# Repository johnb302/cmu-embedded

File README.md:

# cmu-embedded

Zephyr firmware for a small RC car on an **STM32 Nucleo-F401RE**.

A Raspberry Pi reads a steering wheel + pedals and sends commands over UART.
The Nucleo turns those into motor speed, steering, and blinkers — and stops the car safely if the Pi goes quiet.

```
 Steering wheel / pedals
          │
          ▼
   Raspberry Pi ──UART (13-byte frames)──▶ Nucleo F401RE ──▶ motors, servo, blinkers
          ▲                                     │
          └────────── status frames ────────────┘  (current sensors, error state)
```

## File tree

```
.
├── CMakeLists.txt          # What gets compiled (normal firmware or a calibration build)
├── prj.conf                # Zephyr features to enable (GPIO, PWM, ADC, UART, logging)
├── prj_lab3.conf           # Zephyr features for Lab 3 (CAN)
├── zephyr-env.sh           # Sets paths to the local Zephyr SDK/toolchain in .tools/
├── boards/
│   ├── nucleo_f401re.overlay       # Pin map: motors, encoders, servo, blinkers, ADC, UART
│   └── nucleo_f401re_lab3.overlay  # Lab 3 pin map: MCP2515 CAN over SPI
├── src/
│   ├── config.h            # ★ Every tunable number: timings, PID gains, pedal ranges, priorities
│   ├── main.c              # ★ Start here. Receives Pi frames, runs the link watchdog
│   ├── motor_control.c/h   # PID speed loop: pedals → target RPM → PWM
│   ├── motor_driver.c/h    # Low-level L298N H-bridge (drive / brake / coast)
│   ├── encoder.c/h         # Wheel encoders → position + RPM
│   ├── servo_driver.c/h    # Steering servo: steering value → pulse width
│   ├── blinker.c/h         # Turn signals and hazards
│   ├── wheel_buttons.c/h   # Debounces steering-wheel buttons
│   ├── status_tx.c/h       # Sends status frames back to the Pi
│   └── crc8_checksum.h     # CRC-8 shared with the Pi
├── src_lab3/               # Lab 3 dual CAN-bus firmware (built with -DCAN_LAB=ON)
│   ├── lab3.c              # Entry point: N2 steering / N3 drivetrain, chosen by NODE_ID
│   ├── can_bus.c/h         # MCP2515 dual-bus CAN: filters, TX/RX, stall recovery
│   ├── zone_state.c/h      # This zone's OK/ERROR state machine
│   ├── heartbeat.c/h       # Heartbeat TX + monitoring of other zones
│   ├── watchdog.c/h        # Independent watchdog (IWDG), fed only while tasks make progress
│   ├── control.c/h, blink.c/h, button.c/h, n2_tasks.c/h
│   └── tasks.h             # Per-node thread priorities
├── tools/
│   ├── telemetry/          # Live USB dashboard (Python + Matplotlib), logs CSV
│   ├── motor_calibration/  # Separate firmware + script to sweep motor PWM
│   └── servo_calibration/  # Separate firmware + script to find servo endpoints
├── Lab2_Writeup.pdf        # Lab 2 report
└── tests.yaml              # Leftover from the Zephyr blinky sample
```

★ = read these first.

## How the firmware works

Everything runs as Zephyr threads. Lower number = higher priority.

| Priority | Thread         | Job |
| -------: | -------------- | --- |
| 0 | motor          | Every 10 ms: read encoders, run PID, set PWM |
| 1 | fail_safe      | Wakes only if the Pi stops talking → brake + hazards |
| 2 | cmd_handler    | One run per Pi frame: check CRC, apply steer/throttle/brake |
| 3 | status_tx      | Every 20 ms: send current readings + state to the Pi |
| 4 | blinker        | Flashes turn signals / hazards |

One command's path:

1. **UART interrupt** (`main.c`) assembles a 13-byte frame and queues it (only the newest is kept).
2. **cmd_handler** checks the CRC and value ranges, then hands throttle/brake to `motor_control` and steering to `servo_driver`.
3. **Link watchdog**: each good frame restarts a timer. Three missed 50 ms intervals → **fail-safe** (brake, steering off, hazards on).
4. Bad or out-of-range values also trigger fail-safe. The car powers up in fail-safe until the first valid frame.

Frame layout (both directions): `SOF(0xA5) | ID(2) | DLC | data(8) | CRC`.
Command data = steer, throttle, brake (int16 LE), buttons, sequence number.

## Build and flash

```bash
source .venv/bin/activate          # also loads zephyr-env.sh
west build -b nucleo_f401re -p     # normal firmware
west flash
```

Calibration firmware (pick one):

```bash
west build -b nucleo_f401re -p -- -DMOTOR_CALIBRATION=ON
west build -b nucleo_f401re -p -- -DSERVO_CALIBRATION=ON
```

Lab 3 CAN firmware (`src_lab3/`), one build per node:

```bash
west build -b nucleo_f401re -p -d build-lab3-n2 -- -DCAN_LAB=ON -DNODE_ID=2 \
  -DCONF_FILE=prj_lab3.conf -DDTC_OVERLAY_FILE=boards/nucleo_f401re_lab3.overlay
```

Watch it run:

```bash
pip install -r tools/telemetry/requirements.txt
python -u tools/telemetry/telemetry.py --port /dev/ttyACM0
```

## Where to change things

| I want to…                         | Edit |
| ---------------------------------- | ---- |
| Tune PID, max RPM, timeouts        | `src/config.h` |
| Change which pin does what         | `boards/nucleo_f401re.overlay` |
| Turn a Zephyr driver on/off        | `prj.conf` |
| Change frame format                | `src/config.h` **and** the Pi sender |

Motor measurement notes live in `tools/motor_calibration/MEASUREMENTS.md`.

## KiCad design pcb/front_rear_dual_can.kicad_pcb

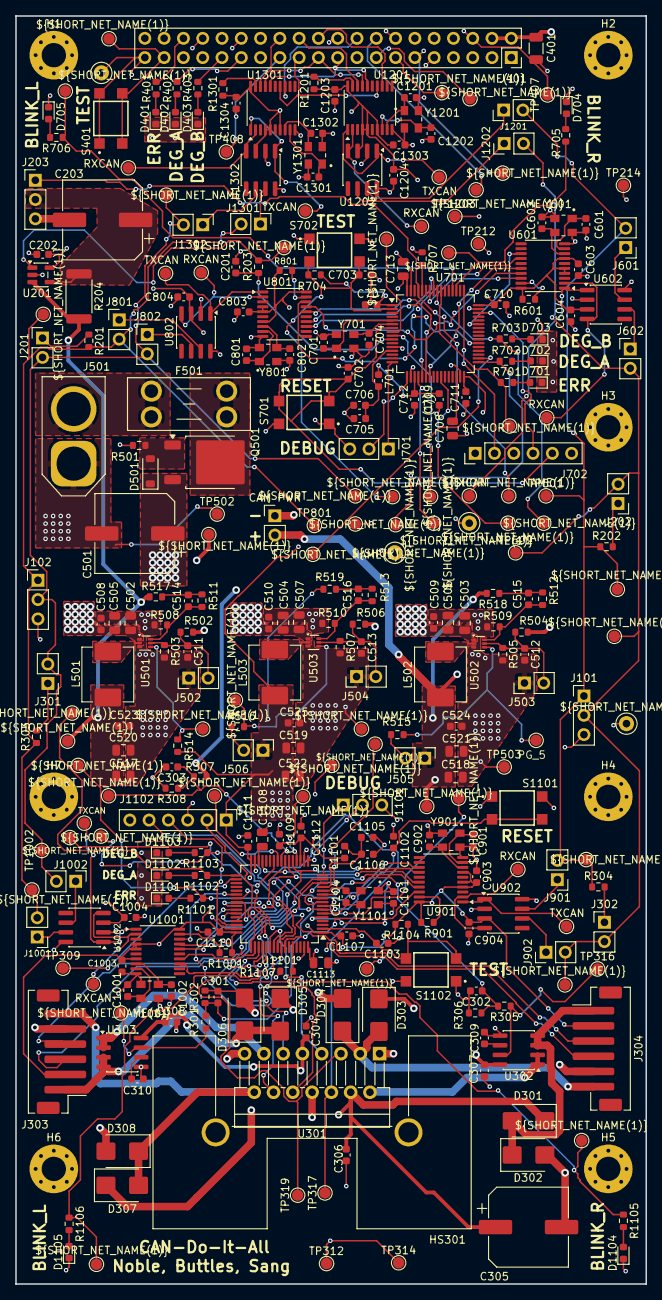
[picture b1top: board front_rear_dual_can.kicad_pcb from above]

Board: 4 copper layers, 83.0 x 167.0 mm, 328 parts (0 on the bottom side), 187 nets.

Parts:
C201, C202, C301, C302, C303, C304, C306, C307, C308, C508, C509, C510, C523, C524, C525, C603, C604, C702, C703, C706, C707, C709, C710, C711, C712, C803, C804, C903, C904, C1003, C1004, C1102, C1103, C1106, C1107, C1109, C1110, C1111, C1112, C1203, C1204, C1303, C1304: 100nF; C_0603_1608Metric
C203, C305, C501: 470μF; CP_Elec_10x12.6
C309, C310: 1nF; C_0603_1608Metric
C401: 47μF; C_1206_3216Metric
C502, C503, C504, C505, C506, C507: 10μF; C_0805_2012Metric
C511, C512, C513: 10nF; C_0603_1608Metric
C514: 33pF; C_0603_1608Metric
C515, C516: 30pF; C_0603_1608Metric
C517, C518, C519, C520, C521, C522: 22μF; C_0805_2012Metric
C601, C602, C701, C704, C801, C802, C901, C902, C1001, C1002, C1101, C1104, C1201, C1202, C1301, C1302: 22pF; C_0603_1608Metric
C705, C1105: 1μF; C_0603_1608Metric
C708, C713, C1108, C1113: 4.7μF; C_0805_2012Metric
CAM PWR: Conn_01x02; PinHeader_1x02_P2.54mm_Vertical
D301, D302, D303, D304, D305, D306, D307, D308: D_Schottky; D_SMB
D401, D402, D403, D701, D702, D703, D704, D705, D1101, D1102, D1103, D1104, D1105: LED; LED_0603_1608Metric
D501: BZT52C10; D_SOD-123
F501: 15A; Fuseholder_Blade_Mini_Keystone_3568
H1, H2, H3, H4, H5, H6, H7: MountingHole_3.2mm_M3_Pad_Via
HS301: HSINK_6396BG
J101: CAN A Connector; PinHeader_1x03_P2.54mm_Vertical
J102: CAN B Connector; PinHeader_1x03_P2.54mm_Vertical
J201, J202, J301, J302, J502, J503, J504, J505, J506: Conn_01x02; PinHeader_1x02_P2.54mm_Vertical
J203, J701, J1101: Conn_01x03; PinHeader_1x03_P2.54mm_Vertical
J303, J304: Conn_01x06; JST_PH_B6B-PH-SM4-TB_1x06-1MP_P2.00mm_Vertical
J401: Raspberry_Pi_4; PinSocket_2x20_P2.54mm_Vertical
J501: XT60; AMASS_XT60-M_1x02_P7.20mm_Vertical
J601, J602, J801, J802, J901, J902, J1001, J1002, J1201, J1202, J1301, J1302: Conn_01x02_Pin; PinHeader_1x02_P2.54mm_Vertical
J702, J1102: Conn_01x06; PinHeader_1x06_P2.54mm_Vertical
L501: 6.8μH; L_Sunlord_MWSA0603S
L502: 4.7μH; L_Sunlord_MWSA0603S
L503: 3.3μH; L_Sunlord_MWSA0603S
L701, L1101: L_Ferrite; L_0603_1608Metric
Q501: IPD90P03P4L-04-HXY; TO-252-2
R201, R202, R303, R304: 120Ω; R_0603_1608Metric
R203: 1kΩ; R_0603_1608Metric
R204: 40mΩ; R_2512_6332Metric
R301, R305, R308, R501, R503, R505, R507, R510, R514, R515, R516, R601, R704, R707, R801, R901, R1001, R1104, R1107, R1201, R1301: 10kΩ; R_0603_1608Metric
R302, R306: 20kΩ; R_0603_1608Metric
R307, R502, R504, R506: 47kΩ; R_0603_1608Metric
R401, R402, R403, R701, R702, R703, R705, R706, R1101, R1102, R1103, R1105, R1106: 330Ω; R_0603_1608Metric
R508, R509: 30kΩ; R_0603_1608Metric
R511: 348kΩ; R_0603_1608Metric
R512: 220kΩ; R_0603_1608Metric
R513: 45.3kΩ; R_0603_1608Metric
R517, R518, R519: 0Ω; R_0603_1608Metric
S401, S701, S702, S1101, S1102: SWT0210-045026GSA_REVA; SW_SWT0210-045026GSA_REVA
TP201, TP202, TP203, TP204, TP205, TP206, TP207, TP208, TP209, TP210, TP211, TP212, TP213, TP214, TP215, TP301, TP302, TP303, TP304, TP305, TP306, TP307, TP308, TP309, TP310, TP311, TP312, TP313, TP314, TP315, TP316, TP317, TP318, TP319, TP402, TP404, TP405, TP406, TP407, TP408, TP410, TP501, TP502, TP503, TP504, TP505, TP506, TP507, TP508, TP509, TP510, TP601, TP602, TP604, TP605, TP801, TP802, TP803, TP804, TP805, TP901, TP902, TP904, TP905, TP1001, TP1002, TP1004, TP1005, TP1201, TP1202, TP1203, TP1204, TP1205, TP1301, TP1302, TP1304, TP1305: TestPoint; TestPoint_Pad_D1.5mm
TP603, TP903, TP1003, TP1303: TestPoint; TestPoint_Keystone_5000-5004_Miniature
U201: INA180A1; SOT-23-5
U301: L298N; TO-220-15_P2.54x5.08mm_StaggerOdd_Lead4.58mm_Vertical
U302, U303: ACS712xLCTR-05B; SOIC-8_3.9x4.9mm_P1.27mm
U501, U502, U503: TPS564252DRLR; SOT-563
U601, U801, U901, U1001, U1201, U1301: MCP2515-xST; TSSOP-20_4.4x6.5mm_P0.65mm
U602, U802, U902, U1002, U1202, U1302: SN65HVD230; SOIC-8_3.9x4.9mm_P1.27mm
U701, U1101: STM32F401RETx; LQFP-64_10x10mm_P0.5mm
Y601, Y701, Y801, Y901, Y1001, Y1101, Y1201, Y1301: CX3225SB16000H0FLJCC; OSCCC320X250X60N

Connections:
+3V3: C202.1, C519.1, C522.1, C525.1, C603.2, C604.1, C707.2, C709.2, C710.1, C711.2, C712.2, C713.1, C803.2, C804.1, C903.2, C904.1, C1003.2, C1004.1, C1107.2, C1109.2, C1110.1, C1111.2, C1112.2, C1113.1, C1203.2, C1204.1, C1303.2, C1304.1, J303.2, J304.2, J506.1, J702.1, J1102.1, L503.2, L701.1, L1101.1, R514.2, R519.2, R601.1, R704.2, R801.1, R901.1, R1001.1, R1104.2, R1201.1, R1301.1, TP510.1 (1_1), U201.5 (V+), U601.4 (~TX0RTS), U601.5 (~TX1RTS), U601.7 (~TX2RTS), U601.20 (VDD), U602.3 (VCC), U701.1 (VBAT), U701.19 (VDD), U701.32 (VDD), U701.48 (VDD), U701.64 (VDD), U801.4 (~TX0RTS), U801.5 (~TX1RTS), U801.7 (~TX2RTS), U801.20 (VDD), U802.3 (VCC), U901.4 (~TX0RTS), U901.5 (~TX1RTS), U901.7 (~TX2RTS), U901.20 (VDD), U902.3 (VCC), U1001.4 (~TX0RTS), U1001.5 (~TX1RTS), U1001.7 (~TX2RTS), U1001.20 (VDD), U1002.3 (VCC), U1101.1 (VBAT), U1101.19 (VDD), U1101.32 (VDD), U1101.48 (VDD), U1101.64 (VDD), U1201.4 (~TX0RTS), U1201.5 (~TX1RTS), U1201.7 (~TX2RTS), U1201.20 (VDD), U1202.3 (VCC), U1301.4 (~TX0RTS), U1301.5 (~TX1RTS), U1301.7 (~TX2RTS), U1301.20 (VDD), U1302.3 (VCC)
+5V: C304.2, C307.1, C308.1, C401.1, C518.1, C521.1, C524.1, CAM PWR.2, J401.2 (5V), J401.4 (5V), J505.1, L502.2, R518.2, TP509.1 (1_1), U301.9 (Vss), U302.8 (VCC), U303.8 (VCC)
+7.5V: C517.1, C520.1, C523.1, L501.2, R204.2, R517.2, TP508.1 (1_1), U201.3 (+)
+12V: C305.1, C306.1, C501.1, C502.1, C503.1, C504.1, C505.1, C506.1, C507.1, C508.1, C509.1, C510.1, D301.1 (K), D303.1 (K), D305.1 (K), D307.1 (K), D501.1 (K), Q501.3 (S), R307.1, R502.1, R504.1, R506.1, TP501.1 (1_1), U301.4 (Vs), U501.1 (VIN), U502.1 (VIN), U503.1 (VIN)
/CAN_A+: J101.1, J601.2, J901.2, J1201.2, R202.1, R304.1, TP601.1 (1_1), TP901.1 (1_1), TP1201.1 (1_1)
/CAN_A-: J101.2, J202.2, J302.2, J602.2, J902.2, J1202.2, TP602.1 (1_1), TP902.1 (1_1), TP1202.1 (1_1)
/CAN_B+: J102.1, J801.2, J1001.2, J1301.2, R201.1, R303.1, TP801.1 (1_1), TP1001.1 (1_1), TP1301.1 (1_1)
/CAN_B-: J102.2, J201.2, J301.2, J802.2, J1002.2, J1302.2, TP802.1 (1_1), TP1002.1 (1_1), TP1302.1 (1_1)
/Cockpit/CAN A/CAN_H_Local: J1201.1, U1202.7 (CANH)
/Cockpit/CAN A/CAN_L_Local: J1202.1, U1202.6 (CANL)
/Cockpit/CAN A/CS: J401.24 (~CE0_SPI0/GPIO08), U1201.18 (~CS)
/Cockpit/CAN A/INT: J401.22 (GPIO25/SDIO_DAT1), U1201.13 (~INT)
/Cockpit/CAN A/OSC1: C1201.1, U1201.9 (OSC1), Y1201.1
/Cockpit/CAN A/OSC2: C1202.1, U1201.8 (OSC2), Y1201.3
/Cockpit/CAN A/SCK: J401.23 (SCLK_SPI0/GPIO11), U1201.14 (SCK), U1301.14 (SCK)
/Cockpit/CAN A/SI: J401.19 (MOSI_SPI0/GPIO10), U1201.16 (SI), U1301.16 (SI)
/Cockpit/CAN A/SO: J401.21 (MISO_SPI0/GPIO09), U1201.17 (SO), U1301.17 (SO)
/Cockpit/CAN B/CAN_H_Local: J1301.1, U1302.7 (CANH)
/Cockpit/CAN B/CAN_L_Local: J1302.1, U1302.6 (CANL)
/Cockpit/CAN B/CS: J401.26 (~CE1_SPI0/GPIO07), U1301.18 (~CS)
/Cockpit/CAN B/INT: J401.18 (GPIO24/SDIO_DAT0), U1301.13 (~INT)
/Cockpit/CAN B/OSC1: C1301.1, U1301.9 (OSC1), Y1301.1
/Cockpit/CAN B/OSC2: C1302.1, U1301.8 (OSC2), Y1301.3
/Cockpit/CAN_TX_A: J401.15 (GPIO22/SDIO_CLK), TP404.1 (1_1)
/Cockpit/CAN_TX_B: J401.16 (GPIO23/SDIO_CMD), TP406.1 (1_1)
/Cockpit/CMD_TX: J401.13 (GPIO27/SDIO_DAT3), TP402.1 (1_1)
/Cockpit/DEG_A: J401.29 (GPCLK1/GPIO05), R402.1
/Cockpit/DEG_B: J401.31 (GPCLK2/GPIO06), R403.1
/Cockpit/ERR: J401.36 (GPIO16/SPI1_~CE2), R401.1
/Cockpit/TEST_BTN: J401.37 (GPIO26/SDIO_DAT2), S401.3, S401.4, TP410.1 (1_1)
/Cockpit/UDP_RX: J401.11 (GPIO17/SPI1_~CE1), TP405.1 (1_1)
/Front Zone/BLINK_L: R706.1, TP208.1 (1_1), U701.52 (PC11)
/Front Zone/BLINK_R: R705.1, TP210.1 (1_1), U701.51 (PC10)
/Front Zone/CAN A/CAN_H_Local: J601.1, U602.7 (CANH)
/Front Zone/CAN A/CAN_L_Local: J602.1, U602.6 (CANL)
/Front Zone/CAN A/CS: U601.18 (~CS), U701.58 (PB6)
/Front Zone/CAN A/INT: U601.13 (~INT), U701.43 (PA10)
/Front Zone/CAN A/OSC1: C601.1, U601.9 (OSC1), Y601.1
/Front Zone/CAN A/OSC2: C602.1, U601.8 (OSC2), Y601.3
/Front Zone/CAN A/SCK: U601.14 (SCK), U701.21 (PA5), U801.14 (SCK)
/Front Zone/CAN A/SI: U601.16 (SI), U701.23 (PA7), U801.16 (SI)
/Front Zone/CAN A/SO: U601.17 (SO), U701.22 (PA6), U801.17 (SO)
/Front Zone/CAN B/CAN_H_Local: J801.1, U802.7 (CANH)
/Front Zone/CAN B/CAN_L_Local: J802.1, U802.6 (CANL)
/Front Zone/CAN B/CS: U701.38 (PC7), U801.18 (~CS)
/Front Zone/CAN B/INT: U701.57 (PB5), U801.13 (~INT)
/Front Zone/CAN B/OSC1: C801.1, U801.9 (OSC1), Y801.1
/Front Zone/CAN B/OSC2: C802.1, U801.8 (OSC2), Y801.3
/Front Zone/CAN_RX_A: TP202.1 (1_1), U701.26 (PB0)
/Front Zone/CAN_RX_B: TP203.1 (1_1), U701.9 (PC1)
/Front Zone/CAN_TX_A: TP205.1 (1_1), U701.8 (PC0)
/Front Zone/CAN_TX_B: TP207.1 (1_1), U701.20 (PA4)
/Front Zone/DEG_A: R702.1, TP204.1 (1_1), U701.33 (PB12)
/Front Zone/DEG_B: R703.1, TP206.1 (1_1), U701.56 (PB4)
/Front Zone/ERR: R701.1, TP201.1 (1_1), U701.55 (PB3)
/Front Zone/I_OUT: R203.2, TP215.1 (1_1), U201.1
/Front Zone/MCU/ADC1_12: C201.1, R203.1, U701.10 (PC2)
/Front Zone/MCU/OSC_IN: C701.1, U701.5 (PH0), Y701.1
/Front Zone/MCU/OSC_OUT: C704.1, U701.6 (PH1), Y701.3
/Front Zone/MCU/RST: C702.2, J702.5, S701.3, S701.4, U701.7 (NRST)
/Front Zone/MCU/SWCLK: J702.2, U701.49 (PA14)
/Front Zone/MCU/SWDIO: J702.4, U701.46 (PA13)
/Front Zone/MCU/USART_RX: J701.2, U701.17 (PA3)
/Front Zone/MCU/USART_TX: J701.1, U701.16 (PA2)
/Front Zone/RELAY: TP209.1 (1_1), U701.34 (PB13)
/Front Zone/SRV: J203.1, TP211.1 (1_1), U701.61 (PB8)
/Front Zone/TEST_BTN: C703.2, R704.1, S702.3, S702.4, TP213.1 (1_1), U701.2 (PC13)
/Power/PG_3.3: R516.1, TP506.1 (1_1), U503.4 (PG)
/Power/PG_5: R515.1, TP507.1 (1_1), U502.4 (PG)
/Power/PG_7.5: R514.1, TP505.1 (1_1), U501.4 (PG)
/Power/SW_3.3: L503.1, U503.2 (SW)
/Power/SW_5: L502.1, U502.2 (SW)
/Power/SW_7.5: L501.1, U501.2 (SW)
/Rear Zone/ADC_IN_L: C301.1, R301.2, R302.1, U1101.10 (PC2)
/Rear Zone/ADC_IN_R: C302.1, R305.2, R306.1, U1101.11 (PC3)
/Rear Zone/BLINK_L: R1106.1, TP308.1 (1_1), U1101.52 (PC11)
/Rear Zone/BLINK_R: R1105.1, TP310.1 (1_1), U1101.51 (PC10)
/Rear Zone/CAN A/CAN_H_Local: J901.1, U902.7 (CANH)
/Rear Zone/CAN A/CAN_L_Local: J902.1, U902.6 (CANL)
/Rear Zone/CAN A/CS: U901.18 (~CS), U1101.58 (PB6)
/Rear Zone/CAN A/INT: U901.13 (~INT), U1101.43 (PA10)
/Rear Zone/CAN A/OSC1: C901.1, U901.9 (OSC1), Y901.1
/Rear Zone/CAN A/OSC2: C902.1, U901.8 (OSC2), Y901.3
/Rear Zone/CAN A/SCK: U901.14 (SCK), U1001.14 (SCK), U1101.21 (PA5)
/Rear Zone/CAN A/SI: U901.16 (SI), U1001.16 (SI), U1101.23 (PA7)
/Rear Zone/CAN A/SO: U901.17 (SO), U1001.17 (SO), U1101.22 (PA6)
/Rear Zone/CAN B/CAN_H_Local: J1001.1, U1002.7 (CANH)
/Rear Zone/CAN B/CAN_L_Local: J1002.1, U1002.6 (CANL)
/Rear Zone/CAN B/CS: U1001.18 (~CS), U1101.38 (PC7)
/Rear Zone/CAN B/INT: U1001.13 (~INT), U1101.57 (PB5)
/Rear Zone/CAN B/OSC1: C1001.1, U1001.9 (OSC1), Y1001.1
/Rear Zone/CAN B/OSC2: C1002.1, U1001.8 (OSC2), Y1001.3
/Rear Zone/CAN_RX_A: TP302.1 (1_1), U1101.26 (PB0)
/Rear Zone/CAN_RX_B: TP303.1 (1_1), U1101.9 (PC1)
/Rear Zone/CAN_TX_A: TP305.1 (1_1), U1101.8 (PC0)
/Rear Zone/CAN_TX_B: TP307.1 (1_1), U1101.20 (PA4)
/Rear Zone/DEG_A: R1102.1, TP304.1 (1_1), U1101.33 (PB12)
/Rear Zone/DEG_B: R1103.1, TP306.1 (1_1), U1101.56 (PB4)
/Rear Zone/DIR_A: TP319.1 (1_1), U301.5 (IN1), U1101.53 (PC12)
/Rear Zone/ENC_L_A: J303.3, U1101.14 (PA0)
/Rear Zone/ENC_L_B: J303.4, U1101.15 (PA1)
/Rear Zone/ENC_R_A: J304.3, U1101.41 (PA8)
/Rear Zone/ENC_R_B: J304.4, U1101.42 (PA9)
/Rear Zone/EN_A: TP317.1 (1_1), U301.6 (EnA), U1101.29 (PB10)
/Rear Zone/ERR: R1101.1, TP301.1 (1_1), U1101.55 (PB3)
/Rear Zone/I_L: R301.1, TP313.1 (1_1), U303.7 (VIOUT)
/Rear Zone/I_R: R305.1, TP316.1 (1_1), U302.7 (VIOUT)
/Rear Zone/MCU/EN_B: U301.11 (EnB), U1101.50 (PA15)
/Rear Zone/MCU/IN2: U301.7 (IN2), U1101.54 (PD2)
/Rear Zone/MCU/IN3: U301.10 (IN3), U1101.39 (PC8)
/Rear Zone/MCU/IN4: U301.12 (IN4), U1101.40 (PC9)
/Rear Zone/MCU/OSC_IN: C1101.1, U1101.5 (PH0), Y1101.1
/Rear Zone/MCU/OSC_OUT: C1104.1, U1101.6 (PH1), Y1101.3
/Rear Zone/MCU/RST: C1102.2, J1102.5, S1101.3, S1101.4, U1101.7 (NRST)
/Rear Zone/MCU/SWCLK: J1102.2, U1101.49 (PA14)
/Rear Zone/MCU/SWDIO: J1102.4, U1101.46 (PA13)
/Rear Zone/MCU/USART_RX: J1101.2, U1101.17 (PA3)
/Rear Zone/MCU/USART_TX: J1101.1, U1101.16 (PA2)
/Rear Zone/M_L+: D305.2 (A), D306.1 (K), J303.1, U303.3 (IP-), U303.4 (IP-)
/Rear Zone/M_L-: D307.2 (A), D308.1 (K), J303.6, U301.14 (OUT4)
/Rear Zone/M_R+: D301.2 (A), D302.1 (K), J304.1, U302.3 (IP-), U302.4 (IP-)
/Rear Zone/M_R-: D303.2 (A), D304.1 (K), J304.6, U301.3 (OUT2)
/Rear Zone/OVERLOAD: TP315.1 (1_1), U1101.25 (PC5)
/Rear Zone/PWM_SET: TP309.1 (1_1), U1101.34 (PB13)
/Rear Zone/TEST_BTN: C1103.2, R1104.1, S1102.3, S1102.4, TP311.1 (1_1), U1101.2 (PC13)
/Rear Zone/VBAT: C303.1, R307.2, R308.1, TP318.1 (1_1), U1101.24 (PC4)
GND: C201.2, C202.2, C203.2, C301.2, C302.2, C303.2, C304.1, C305.2, C306.2, C307.2, C308.2, C309.1, C310.2, C401.2, C501.2, C502.2, C503.2, C504.2, C505.2, C506.2, C507.2, C508.2, C509.2, C510.2, C511.2, C512.2, C513.2, C517.2, C518.2, C519.2, C520.2, C521.2, C522.2, C523.2, C524.2, C525.2, C601.2, C602.2, C603.1, C604.2, C701.2, C702.1, C703.1, C704.2, C705.2, C706.1, C707.1, C708.1, C709.1, C710.2, C711.1, C712.1, C713.2, C801.2, C802.2, C803.1, C804.2, C901.2, C902.2, C903.1, C904.2, C1001.2, C1002.2, C1003.1, C1004.2, C1101.2, C1102.1, C1103.1, C1104.2, C1105.2, C1106.1, C1107.1, C1108.1, C1109.1, C1110.2, C1111.1, C1112.1, C1113.2, C1201.2, C1202.2, C1203.1, C1204.2, C1301.2, C1302.2, C1303.1, C1304.2, CAM PWR.1, D302.2 (A), D304.2 (A), D306.2 (A), D308.2 (A), D401.1 (K), D402.1 (K), D403.1 (K), D701.1 (K), D702.1 (K), D703.1 (K), D704.1 (K), D705.1 (K), D1101.1 (K), D1102.1 (K), D1103.1 (K), D1104.1 (K), D1105.1 (K), J101.3, J102.3, J203.3, J303.5, J304.5, J401.6 (GND), J401.9 (GND), J401.14 (GND), J401.20 (GND), J401.25 (GND), J401.30 (GND), J401.34 (GND), J401.39 (GND), J501.1, J502.1, J503.1, J504.1, J701.3, J702.3, J1101.3, J1102.3, R302.2, R306.2, R308.2, R501.2, R503.2, R505.2, R507.2, R508.1, R509.1, R510.1, R707.1, R1107.1, S401.1, S401.2, S701.1, S701.2, S702.1, S702.2, S1101.1, S1101.2, S1102.1, S1102.2, TP212.1 (1_1), TP214.1 (1_1), TP312.1 (1_1), TP314.1 (1_1), TP407.1 (1_1), TP408.1 (1_1), TP502.1 (1_1), TP503.1 (1_1), TP504.1 (1_1), TP603.1, TP803.1 (1_1), TP903.1, TP1003.1, TP1203.1 (1_1), TP1303.1, U201.2 (GND), U301.1 (SENSE_A), U301.8 (GND), U301.15 (SENSE_B), U302.5 (GND), U303.5 (GND), U501.3 (GND), U502.3 (GND), U503.3 (GND), U601.10 (VSS), U602.2 (GND), U602.8 (Rs), U701.12 (VSSA), U701.18 (VSS), U701.31 (VSS), U701.47 (VSS), U701.63 (VSS), U801.10 (VSS), U802.2 (GND), U802.8 (Rs), U901.10 (VSS), U902.2 (GND), U902.8 (Rs), U1001.10 (VSS), U1002.2 (GND), U1002.8 (Rs), U1101.12 (VSSA), U1101.18 (VSS), U1101.31 (VSS), U1101.47 (VSS), U1101.63 (VSS), U1201.10 (VSS), U1202.2 (GND), U1202.8 (Rs), U1301.10 (VSS), U1302.2 (GND), U1302.8 (Rs), Y601.2 (GND), Y601.4 (GND), Y701.2 (GND), Y701.4 (GND), Y801.2 (GND), Y801.4 (GND), Y901.2 (GND), Y901.4 (GND), Y1001.2 (GND), Y1001.4 (GND), Y1101.2 (GND), Y1101.4 (GND), Y1201.2 (GND), Y1201.4 (GND), Y1301.2 (GND), Y1301.4 (GND)
unnamed: C514.2, R511.2, R517.1
unnamed: C515.2, R512.2, R518.1
unnamed: C516.2, R513.2, R519.1
unnamed: D401.2 (A), R401.2
unnamed: D402.2 (A), R402.2
unnamed: D403.2 (A), R403.2
unnamed: D501.2 (A), Q501.1 (G), R501.1
unnamed: D701.2 (A), R701.2
unnamed: D702.2 (A), R702.2
unnamed: D703.2 (A), R703.2
unnamed: D704.2 (A), R705.2
unnamed: D705.2 (A), R706.2
unnamed: D1101.2 (A), R1101.2
unnamed: D1102.2 (A), R1102.2
unnamed: D1103.2 (A), R1103.2
unnamed: D1104.2 (A), R1105.2
unnamed: D1105.2 (A), R1106.2
unnamed: J201.1, R201.2
unnamed: J202.1, R202.2
unnamed: C203.1, J203.2, R204.1, U201.4 (-)
unnamed: J301.1, R303.2
unnamed: J302.1, R304.2
unnamed: F501.1, J501.2
unnamed: C511.1, J502.2, R502.2, R503.1, U501.5 (EN)
unnamed: C512.1, J503.2, R504.2, R505.1, U502.5 (EN)
unnamed: C513.1, J504.2, R506.2, R507.1, U503.5 (EN)
unnamed: J505.2, R515.2
unnamed: J506.2, R516.2
unnamed: F501.2, Q501.2 (D)
unnamed: U301.2 (OUT1), U302.1 (IP+), U302.2 (IP+)
unnamed: U301.13 (OUT3), U303.1 (IP+), U303.2 (IP+)
unnamed: C309.2, U302.6 (FILTER)
unnamed: C310.1, U303.6 (FILTER)
unnamed: C514.1, R508.2, R511.1, U501.6 (FB)
unnamed: C515.1, R509.2, R512.1, U502.6 (FB)
unnamed: C516.1, R510.2, R513.1, U503.6 (FB)
unnamed: TP604.1 (1_1), U601.2 (RXCAN), U602.4 (R)
unnamed: TP605.1 (1_1), U601.1 (TXCAN), U602.1 (D)
unnamed: R601.2, U601.19 (~RESET)
unnamed: R707.2, U701.60 (BOOT0)
unnamed: C708.2, U701.30 (VCAP1)
unnamed: C705.1, C706.2, L701.2, U701.13 (VREF+)
unnamed: TP804.1 (1_1), U801.2 (RXCAN), U802.4 (R)
unnamed: TP805.1 (1_1), U801.1 (TXCAN), U802.1 (D)
unnamed: R801.2, U801.19 (~RESET)
unnamed: TP904.1 (1_1), U901.2 (RXCAN), U902.4 (R)
unnamed: TP905.1 (1_1), U901.1 (TXCAN), U902.1 (D)
unnamed: R901.2, U901.19 (~RESET)
unnamed: TP1004.1 (1_1), U1001.2 (RXCAN), U1002.4 (R)
unnamed: TP1005.1 (1_1), U1001.1 (TXCAN), U1002.1 (D)
unnamed: R1001.2, U1001.19 (~RESET)
unnamed: R1107.2, U1101.60 (BOOT0)
unnamed: C1108.2, U1101.30 (VCAP1)
unnamed: C1105.1, C1106.2, L1101.2, U1101.13 (VREF+)
unnamed: TP1204.1 (1_1), U1201.2 (RXCAN), U1202.4 (R)
unnamed: TP1205.1 (1_1), U1201.1 (TXCAN), U1202.1 (D)
unnamed: R1201.2, U1201.19 (~RESET)
unnamed: TP1304.1 (1_1), U1301.2 (RXCAN), U1302.4 (R)
unnamed: TP1305.1 (1_1), U1301.1 (TXCAN), U1302.1 (D)
unnamed: R1301.2, U1301.19 (~RESET)

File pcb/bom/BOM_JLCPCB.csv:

Comment,Designator,Footprint,LCSC Part #
100nF,"C201,C202,C301,C302,C303,C304,C307,C308,C523,C524,C525,C603,C604,C702,C703,C706,C707,C709,C710,C711,C712,C803,C804,C903,C904,C1003,C1004,C1102,C1103,C1106,C1107,C1109,C1110,C1111,C1112,C1203,C1204,C1303,C1304",C_0603_1608Metric,C18522636
470μF,"C203,C305,C501",CP_Elec_10x12.6,C1517666
100nF 50V,"C306,C508,C509,C510",C_0603_1608Metric,C14663
1nF,"C309,C310",C_0603_1608Metric,C2219251
47μF,C401,C_1206_3216Metric,C96123
10μF,"C502,C503,C504,C505,C506,C507",C_0805_2012Metric,C15850
10nF,"C511,C512,C513",C_0603_1608Metric,C1589
33pF,C514,C_0603_1608Metric,C107047
30pF,"C515,C516",C_0603_1608Metric,C113797
22μF,"C517,C518,C519,C520,C521,C522",C_0805_2012Metric,C162295
22pF,"C601,C602,C701,C704,C801,C802,C901,C902,C1001,C1002,C1101,C1104,C1201,C1202,C1301,C1302",C_0603_1608Metric,C2168649
1μF,"C705,C1105",C_0603_1608Metric,C519560
4.7μF,"C708,C713,C1108,C1113",C_0805_2012Metric,C408144
D_Schottky,"D301,D302,D303,D304,D305,D306,D307,D308",D_SMB,C139681
LED_Red,"D401,D402,D403,D701,D702,D703,D1101,D1102,D1103",LED_0603_1608Metric,C94869
BZT52C10,D501,D_SOD-123,C173431
LED_Yellow,"D704,D705,D1104,D1105",LED_0603_1608Metric,C125095
15A,F501,Fuseholder_Blade_Mini_Keystone_3568,C5249699
CAN A Connector,J101,PinHeader_1x03_P2.54mm_Vertical,C2937625
CAN B Connector,J102,PinHeader_1x03_P2.54mm_Vertical,C2937625
Conn_01x02,"J201,J202,J301,J302,J502,J503,J504,J505,J506",PinHeader_1x02_P2.54mm_Vertical,C492401
Conn_01x03,"J203,J701,J1101",PinHeader_1x03_P2.54mm_Vertical,C2937625
Conn_01x06 B6B-PH-SM4-TB,"J303,J304",JST_PH_B6B-PH-SM4-TB_1x06-1MP_P2.00mm_Vertical,C471518
Raspberry_Pi_4,J401,PinSocket_2x20_P2.54mm_Vertical,C5124634
XT60,J501,AMASS_XT60-M_1x02_P7.20mm_Vertical,C98733
Conn_01x02_Pin,"J601,J602,J801,J802,J901,J902,J1001,J1002,J1201,J1202,J1301,J1302",PinHeader_1x02_P2.54mm_Vertical,C492401
Conn_01x06 PZ254V-11-06P,"J702,J1102",PinHeader_1x06_P2.54mm_Vertical,C492405
6.8μH,L501,L_Sunlord_MWSA0603S,C408449
4.7μH,L502,L_Sunlord_MWSA0603S,C408447
3.3μH,L503,L_Sunlord_MWSA0603S,C408446
L_Ferrite,"L701,L1101",L_0603_1608Metric,C2650942
IPD90P03P4L-04-HXY,Q501,TO-252-2,C20606270
120Ω,"R201,R202,R303,R304",R_0603_1608Metric,C114640
1kΩ,R203,R_0603_1608Metric,C118155
40mΩ,R204,R_2512_6332Metric,C844291
10kΩ,"R301,R305,R308,R501,R503,R505,R507,R510,R514,R515,R516,R601,R704,R707,R801,R901,R1001,R1104,R1107,R1201,R1301",R_0603_1608Metric,C844918
20kΩ,"R302,R306",R_0603_1608Metric,C4184
47kΩ,"R307,R502,R504,R506",R_0603_1608Metric,C105579
330Ω,"R401,R402,R403,R701,R702,R703,R705,R706,R1101,R1102,R1103,R1105,R1106",R_0603_1608Metric,C105881
30kΩ,"R508,R509",R_0603_1608Metric,C22984
348kΩ,R511,R_0603_1608Metric,C23006
220kΩ,R512,R_0603_1608Metric,C22961
45.3kΩ,R513,R_0603_1608Metric,C23058
0Ω,"R517,R518,R519",R_0603_1608Metric,C95177
SWT0210-045026GSA_REVA,"S401,S701,S702,S1101,S1102",SW_SWT0210-045026GSA_REVA,
TestPoint,"TP309,TP316,TP317,TP319,TP407,TP601,TP602,TP801,TP1002",TestPoint_Keystone_5015_Micro_Mini,C2906768
TestPoint (5001),"TP212,TP214,TP312,TP314,TP408,TP502,TP503,TP603,TP903,TP1003,TP1203,TP1303",TestPoint_Keystone_5000-5004_Miniature,C238122
INA180A1,U201,SOT-23-5,C122228
L298N,U301,TO-220-15_P2.54x5.08mm_StaggerOdd_Lead4.58mm_Vertical,C434589
ACS712xLCTR-05B,"U302,U303",SOIC-8_3.9x4.9mm_P1.27mm,C44471
TPS564252DRLR,"U501,U502,U503",SOT-563,C19191267
MCP2515-xST,"U601,U801,U901,U1001,U1201,U1301",TSSOP-20_4.4x6.5mm_P0.65mm,C185941
SN65HVD230,"U602,U802,U902,U1002,U1202,U1302",SOIC-8_3.9x4.9mm_P1.27mm,C2878159
STM32F401RETx,"U701,U1101",LQFP-64_10x10mm_P0.5mm,C2053837
CX3225SB16000H0FLJCC,"Y601,Y701,Y801,Y901,Y1001,Y1101,Y1201,Y1301",OSCCC320X250X60N,C1985207
